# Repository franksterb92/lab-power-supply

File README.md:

# lab-power-supply
this is still vary much a work in progress im putting this
up as a test this will be a kit ill sell or if u wanna make 
it ill put all info in this repository . again be carfull
with the pcb files im still prototyping so some stuff might
not work corectly

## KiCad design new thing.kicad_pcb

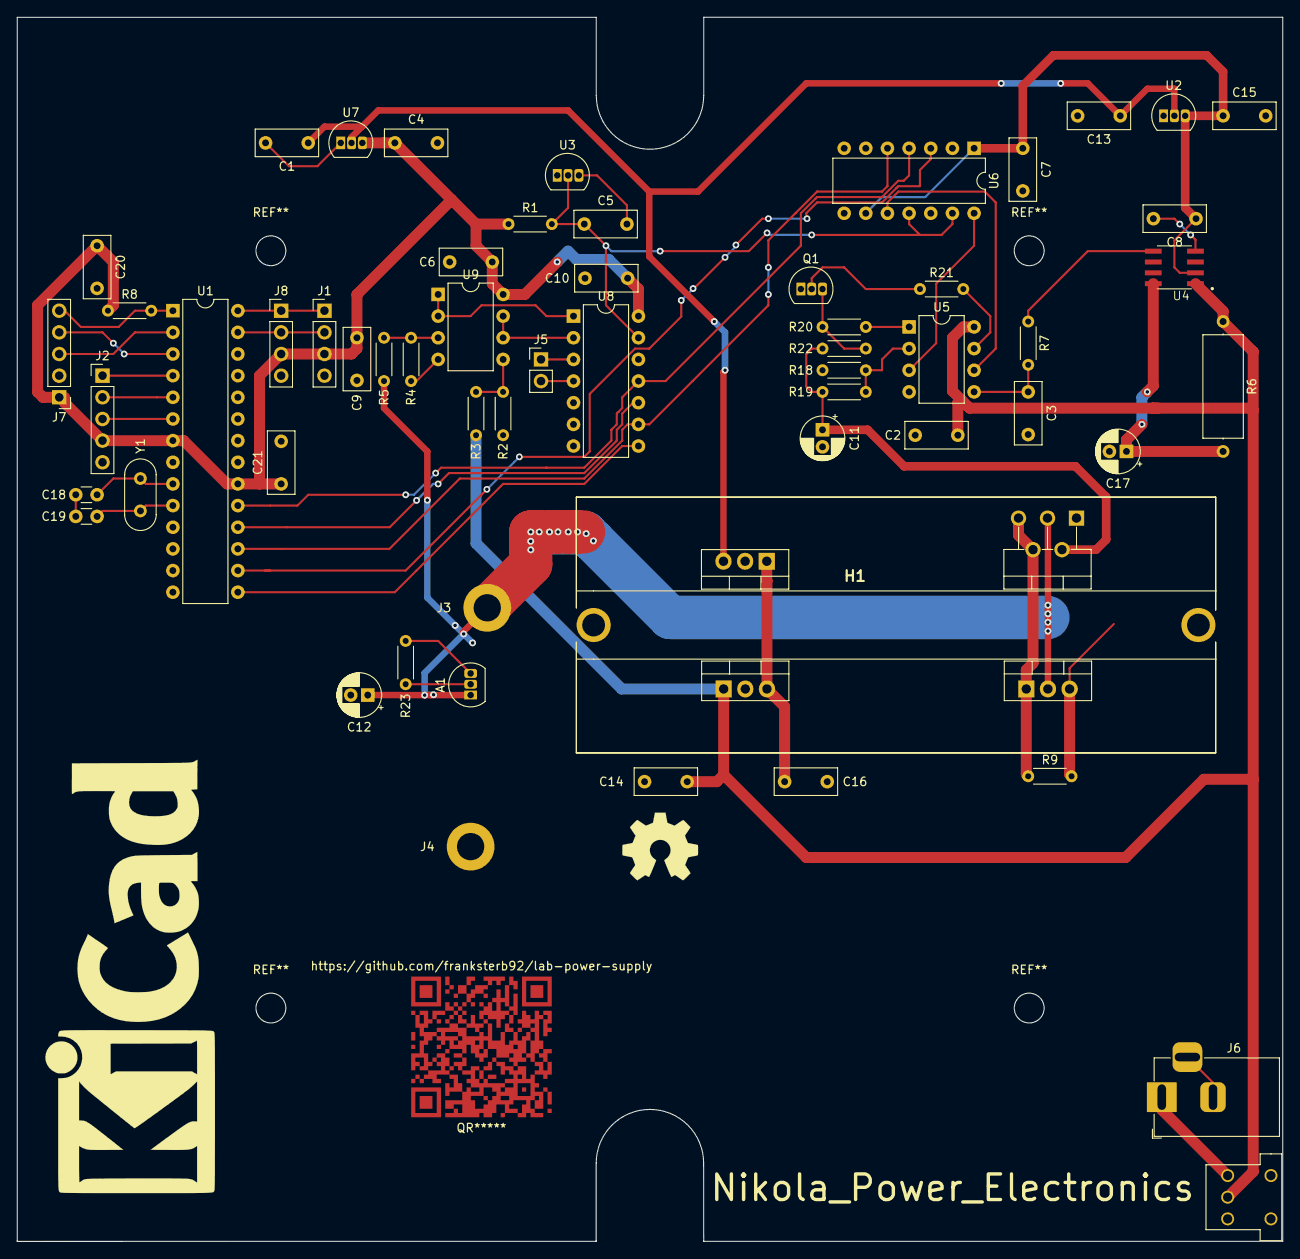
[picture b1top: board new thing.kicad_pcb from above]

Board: 2 copper layers, 148.4 x 143.6 mm, 59 parts (0 on the bottom side), 43 nets.

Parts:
A1: LM334Z_NOPB; TO-92L
C1, C4, C5, C9, C13, C14, C15, C16: 10uF; C_Rect_L7.2mm_W3.0mm_P5.00mm_FKS2_FKP2_MKS2_MKP2
C2, C6, C7, C8, C10: 100n; C_Rect_L7.2mm_W3.0mm_P5.00mm_FKS2_FKP2_MKS2_MKP2
C3: 1uF; C_Rect_L7.2mm_W3.0mm_P5.00mm_FKS2_FKP2_MKS2_MKP2
C11: 20uF; CP_Radial_D5.0mm_P2.00mm
C12, C17: 2.2uF; CP_Radial_D5.0mm_P2.00mm
C18, C19: CP; C_Disc_D3.0mm_W1.6mm_P2.50mm
C20, C21: CP; C_Rect_L7.2mm_W3.0mm_P5.00mm_FKS2_FKP2_MKS2_MKP2
H1: Heatsink_For_lab_power_supply; OMNIUNI3075D_TO220_Heatsink
J1: LCD_CONN; PinHeader_1x04_P2.54mm_Vertical
J2: ENCODER_CONN; PinHeader_1x05_P2.54mm_Vertical
J3, J4: Output; MountingHole_3.2mm_M3_DIN965_Pad
J5: ADC_CONN; PinHeader_1x02_P2.54mm_Vertical
J6: Barrel_Jack_Switch; BarrelJack_Horizontal
J7: Program_CONN; PinHeader_1x05_P2.54mm_Vertical
J8: FRONT_CONN; PinHeader_1x04_P2.54mm_Vertical
Q1: 2N3904; TO-92L
QR*****: https://github.com/franksterb92/lab-power-supply; QR_Test
R1: 45k; R_Axial_0.25W
R2, R3, R4, R5: R; R_Axial_0.25W
R6: 0.2R; R_Axial_ALSR3F
R7: 330R; R_Axial_0.25W
R8: 10k; R_Axial_0.25W
R9: 50K; R_Axial_0.25W
R18, R21: 10K; R_Axial_0.25W
R19: 30K; R_Axial_0.25W
R20, R22: 1K; R_Axial_0.25W
R23: 100R; R_Axial_DIN0204_L3.6mm_D1.6mm_P5.08mm_Horizontal
SW2: SW_SPDT; 500ASSP1M6QE_SPDT
U1: ATMEGA328P-PU; DIP-28_W7.62mm
U2, U7: MCP1700_5.0V; TO-92L
U3: LT1634-4.096; TO-92L
U4: Max4080F; Max4080f_SOIC8
U5, U9: LM358; DIP-8_W7.62mm
U6: MCP4922-E_P; DIP-14_W7.62mm
U8: MCP3204-CI_P; DIP-14_W7.62mm
Y1: Crystal; Crystal_HC52-6mm_Vertical

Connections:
/5V: C1.1, C13.1, H1.16, U2.2, U7.2
/ADC0: U8.1, U9.1, U9.2
/ADC1: U8.2, U9.6, U9.7
/ADC_3: J5.1, U8.3
/ADC_4: J5.2, U8.4
/ADC_CS: U1.15, U8.8
/ADC_VIN: R2.1, R3.2, U9.5
/ADC_VOUT: R4.2, R5.2, U9.3
/CLK: U1.19, U6.4, U8.11
/Curent_Lim: Q1.2, R21.1
/DAC_CS: U1.16, U6.3
/ENC_CLK: J2.1, U1.4
/ENC_DT: J2.2, U1.5
/ENC_SW: J2.3, U1.6
/ISETDAC: U5.6, U6.10
/LCD_SCL: J1.1, J8.1, U1.28
/LCD_SDA: J1.2, J8.2, U1.27
/MISO: U1.18, U8.10
/MOSI: U1.17, U6.5, U8.9
/Output: A1.1, C12.1, H1.7, H1.11, J3.1, R5.1
/Prog+5V: C4.1, C6.1, C9.1, C10.1, C20.1, C21.1, J1.3, J2.4, J7.1, J8.3, R1.1, R8.1, U1.7, U1.20, U7.3, U8.14, U9.8
/Prog_Reset: J7.5, R8.2, U1.1
/RX: J7.4, U1.3
/SET: C11.1, R19.2, R22.1
/TO_LT3080: C17.1, R6.2, R9.2
/TO_REG: H1.6, H1.12, H1.13
/TO_TRAN: H1.8, U4.8
/TX: J7.3, U1.2
/VREF: C5.1, R1.2, U3.2, U6.11, U6.13, U8.13
/VSETDAC: U5.3, U6.14
/max4080: C7.1, C8.1, C15.1, U2.3, U4.2, U6.1, U6.9
/to_reg: C16.1, H1.5, H1.14
GNDA: A1.3, C1.2, C2.2, C3.2, C4.2, C5.2, C6.2, C7.2, C8.2, C9.2, C10.2, C11.2, C12.2, C13.2, C14.2, C15.2, C16.2, C17.2, C18.2, C19.2, C20.2, C21.2, H1.4, H1.15, J1.4, J2.5, J4.1, J6.2, J6.3, J7.2, J8.4, Q1.1, R2.2, R4.1, R18.2, R23.2, U1.8, U1.22, U2.1, U3.3, U4.4, U5.4, U6.8, U6.12, U7.1, U8.7, U8.12, U9.4
unnamed: C3.1, R7.2, U5.5
unnamed: C18.1, U1.9, Y1.1
unnamed: C19.1, U1.10, Y1.2
unnamed: J6.1, SW2.1
unnamed: Q1.3, R20.1, R22.2
unnamed: R7.1, U4.5
unnamed: R18.1, R19.1, U5.2
unnamed: R20.2, U5.1
unnamed: R21.2, U5.7
VCC: C2.1, C14.1, H1.3, R3.1, R6.1, SW2.2, U4.1, U5.8

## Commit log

2021-01-31 Create v1.0 power supply code
    this version has a bug wen u set voltage to say 0.5 then go to current and it will immediately go to 0.6
